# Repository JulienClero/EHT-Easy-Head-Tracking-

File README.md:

# EHT (Easy Head Tracking)

A DIY head tracking system using ESP32 and MPU6050 for gaming and simulations, compatible with OpenTrack.

## 🎯 Features

- **3DOF Tracking**: Yaw, Pitch, Roll with gyroscope, accelerometer and magnetometer
- **WiFi Transmission**: Real-time UDP data streaming
- **Complementary Filter**: Eliminates drift on pitch/roll
- **Start Up Yaw Calibartion**: Minimizes yaw drift
- **Low Latency**: Less than 20ms end-to-end
- **OpenTrack Compatible**: Plug & play with games and simulators

## 🔧 Components

### Current Version (v1.0)
- **ESP32** (DevKit v1 or similar) - ~$8
- **MPU6050** (accelerometer + gyroscope) - ~$3
- **4 jumper wires** female-female - ~$2
- **Case/mount** (3D printing recommended) - ~$2

### Future Version (v2.0) - In Development
- **ESP32-S3 N4** - ~$3.8 (JLCPCB)
- **ICM-20948** (9-axis, accelerometer + gyroscope + magnetometer) - ~$4.5
- **EHT Custom PCB** (currently being designed)
- **Li-Ion Battery** (500-1000mAh)
- **Charging Circuit** (integrated PCB)
- **ON/OFF Switch**
- **Custom Case** (3D printed) - <$1

## 📐 Wiring Diagram

### Version v1.0 (Prototype)
```
ESP32          MPU6050
-----          -------
3.3V    ---    VCC
GND     ---    GND
GPIO21  ---    SDA
GPIO22  ---    SCL
```

### Version v2.0 (Custom PCB)
*Detailed schematic available with custom PCB*

## 🚀 Installation

### 1. Prepare Environment
```bash
# Install Arduino IDE
# Add ESP32 support:
# File > Preferences > Additional Board Manager URLs
# https://dl.espressif.com/dl/package_esp32_index.json
```

### 2. Configure Code
```cpp
// Modify these variables in the code:
const char* ssid     = "YOUR_WIFI";
const char* password = "YOUR_PASSWORD";
IPAddress pcIP(192, 168, 1, XXX);  // Your PC IP
```

### 3. Flash ESP32
- Select board: `ESP32 Dev Module`
- Select serial port
- Make modifications to the code : Fill in your wifi ssid, password and your PC's IP adress (2. Configure Code)
- Compile and upload

## 🎮 OpenTrack Configuration

### 1. Install OpenTrack
Download from: https://github.com/opentrack/opentrack/releases

### 2. Configuration
1. **Input**: `UDP over network`
   - Port: `4242`
   - Bind address: `0.0.0.0`

2. **Output**: Choose according to your game
   - `freetrack 2.0 Enhanced` (most games)
   - `TrackIR` (for compatible games)

3. **Mapping**: Adjust to your preferences

### 3. Use
- Switch on your EHT
- Stay still while it calibrates (10 sec default)
- Start OpenTrack
- Click "Start"
- You should see the octopus move with your head

## 📊 Performance

- **Frequency**: 100Hz (10ms per sample)
- **Total Latency**: < 20ms
- **Accuracy**: ±1° (pitch/roll), ±2° (yaw)
- **Drift**: None on pitch/roll, slight on yaw

## 🔧 Advanced Settings (v1.0)

### Sensitivity Adjustment
```cpp
// In code, final lines:
headData[0] = yaw * 2.0;   // Multiply for more sensitivity
headData[1] = pitch * 3.0;
headData[2] = roll * 3.0;
```

### Complementary Filter
```cpp
const float alpha = 0.99f;  // 0.95-0.99 recommended
// Closer to 1.0 = more responsive but more noise
// Closer to 0.9 = more stable but less responsive
```

## 🛠️ Troubleshooting

### WiFi Connection Issues
- Check SSID/password
- Verify ESP32 is on same network
- Restart router if necessary

### Angle Drift
- **Pitch/Roll**: No drift (complementary filter)
- **Yaw**: Normal drift without magnetometer
- Solution: Recalibrate with `Ctrl+Home` in OpenTrack

### Erratic Data
- Check I2C connections
- Add decoupling capacitors if needed
- Verify stable 3.3V power supply

### High Latency
- Reduce `LOOP_INTERVAL_MS` (watch CPU load)
- Use 5GHz WiFi if possible
- Disable WiFi sleep mode

## 🤝 Contributing

Contributions are welcome! Feel free to:
- Report bugs
- Suggest improvements
- Share hardware modifications
- Add support for more games

## 📄 License

See the `LICENSE` file for details.

## 🎮 Tested Games

- ✅ **DCS World** (freetrack)
- ✅ **Star Citizen** (freetrack)

## 🔮 Roadmap

### Version 1.0 (Current) ✅
- [x] 3DOF tracking (Yaw, Pitch, Roll)
- [x] WiFi UDP transmission
- [x] Complementary filter
- [x] Yaw Calibration
- [x] OpenTrack compatibility

### Version 2.0 (Planned)
- [ ] **EHT Custom PCB** - Compact and professional design
- [ ] **Magnetometer support** - Eliminates yaw drift
- [ ] **Integrated battery** - 8-12h autonomy
- [ ] **USB-C charging circuit** - Fast charging
- [ ] **Status LEDs or Small OLED Screen** - Battery, WiFi, tracking

---

**⚠️ Important**: This project is for personal use. Please respect the terms of use of games and simulators.

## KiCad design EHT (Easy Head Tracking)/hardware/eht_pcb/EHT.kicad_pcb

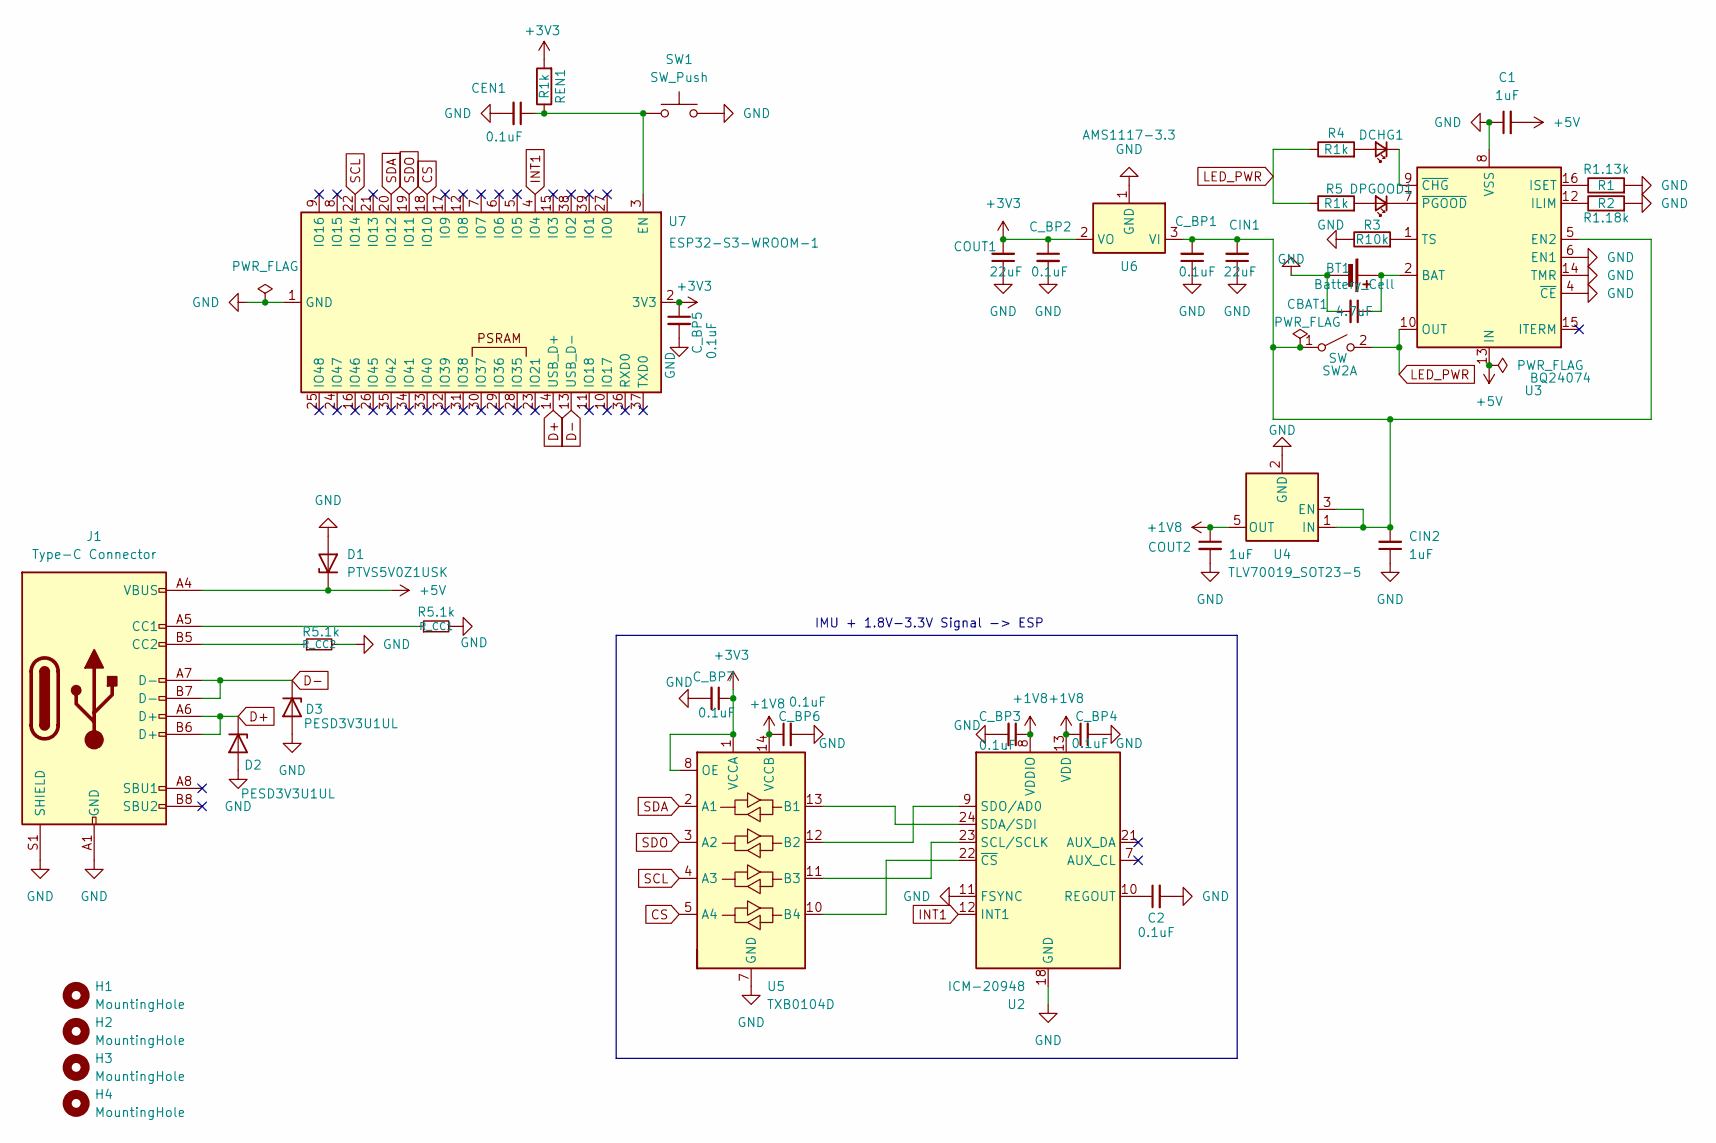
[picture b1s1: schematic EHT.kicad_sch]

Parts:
BT1: Battery_Cell
C1: 1uF; C_0603_1608Metric
C2: 0.1uF; C_0603_1608Metric
CBAT1: 4.7uF; C_0603_1608Metric
CEN1: 0.1uF; C_0603_1608Metric
CIN1: 22uF; C_0603_1608Metric
CIN2: 1uF; C_0603_1608Metric
COUT1: 22uF; C_0603_1608Metric
COUT2: 1uF; C_0603_1608Metric
C_BP1, C_BP2, C_BP3, C_BP4, C_BP5, C_BP6, C_BP7: 0.1uF; C_0603_1608Metric
D1: PTVS5V0Z1USK; Nexperia_DSN1608-2_1.6x0.8mm
D2, D3: PESD3V3U1UL; D_SOD-882
DCHG1: LED; LED_0805_2012Metric
DPGOOD1: LED; LED_0805_2012Metric
H1, H2, H3, H4: MountingHole; MountingHole_2.2mm_M2
J1: Type-C Connector; USB_C_Receptacle_GCT_USB4105-xx-A_16P_TopMnt_Horizontal
R1: R1.13k; R_0603_1608Metric
R2: R1.18k; R_0603_1608Metric
R3: R10k; R_0603_1608Metric
R4, R5: R1k; R_0603_1608Metric
REN1: R1k; R_0603_1608Metric
R_CC1, R_CC2: R5.1k; R_0603_1608Metric
SW1: SW_Push; SW_PUSH_1P1T_6x3.5mm_H4.3_APEM_MJTP1243
SW2: SW; SW_DIP_SPSTx01_Slide_Copal_CHS-01A_W5.08mm_P1.27mm_JPin
U2: ICM-20948; InvenSense_QFN-24_3x3mm_P0.4mm
U3: BQ24074; VQFN-16-1EP_3x3mm_P0.5mm_EP1.6x1.6mm
U4: TLV70019_SOT23-5; SOT-23-5
U5: TXB0104D; SOIC-14_3.9x8.7mm_P1.27mm
U6: AMS1117-3.3; SOT-223-3_TabPin2
U7: ESP32-S3-WROOM-1

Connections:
+1V8: COUT2.1, C_BP3.1, C_BP4.1, C_BP6.1, U2.8 (VDDIO), U2.13 (VDD), U4.5 (OUT), U5.14 (VCCB)
+3V3: COUT1.2, C_BP2.1, C_BP5.1, C_BP7.1, REN1.2, U5.1 (VCCA), U5.8 (OE), U6.2 (VO), U7.2 (3V3)
+5V: C1.2, D1.1 (K), J1.A4 (VBUS), J1.A9 (VBUS), J1.B4 (VBUS), J1.B9 (VBUS), U3.13 (IN)
CS: U5.5 (A4), U7.18 (IO10)
D+: D2.1 (K), J1.A6 (D+), J1.B6 (D+), U7.14 (USB_D+)
D-: D3.1 (K), J1.A7 (D-), J1.B7 (D-), U7.13 (USB_D-)
GND: BT1.2 (-), C1.1, C2.2, CBAT1.2, CEN1.2, CIN1.1, CIN2.1, COUT1.1, COUT2.2, C_BP1.1, C_BP2.2, C_BP3.2, C_BP4.2, C_BP5.2, C_BP6.2, C_BP7.2, D1.2 (A), D2.2 (A), D3.2 (A), J1.A1 (GND), J1.A12 (GND), J1.B1 (GND), J1.B12 (GND), J1.S1 (SHIELD), R1.2, R2.2, R3.1, R_CC1.2, R_CC2.2, SW1.2, U2.11 (FSYNC), U2.18 (GND), U2.20 (GND), U3.4 (~CE), U3.6 (EN1), U3.8 (VSS), U3.14 (TMR), U3.17 (VSS), U4.2 (GND), U5.7 (GND), U6.1 (GND), U7.1 (GND), U7.40 (GND), U7.41 (GND); also elsewhere on the board
INT1: U2.12 (INT1), U7.4 (IO4)
LED_PWR: R4.1, R5.1, SW2.2 (B), U3.10 (OUT), U3.11 (OUT)
unnamed 9: BT1.1 (+), CBAT1.1, U3.2 (BAT), U3.3 (BAT); also elsewhere on the board
unnamed: DCHG1.2 (A), R4.2
unnamed: DCHG1.1 (K), U3.9 (~CHG)
unnamed: DPGOOD1.2 (A), R5.2
unnamed: DPGOOD1.1 (K), U3.7 (~PGOOD)
unnamed: J1.A5 (CC1), R_CC1.1
unnamed: J1.B5 (CC2), R_CC2.1
unnamed: CIN1.2, CIN2.2, C_BP1.2, SW2.1 (A), U3.5 (EN2), U4.1 (IN), U4.3 (EN), U6.3 (VI)
unnamed: C2.1, U2.10 (REGOUT)
unnamed: U2.23 (SCL/SCLK), U5.11 (B3)
unnamed: U2.24 (SDA/SDI), U5.13 (B1)
unnamed: U2.9 (SDO/AD0), U5.12 (B2)
unnamed: U2.22 (~CS), U5.10 (B4)
unnamed: R2.1, U3.12 (ILIM)
unnamed: R1.1, U3.16 (ISET)
unnamed: R3.2, U3.1 (TS)
unnamed: CEN1.1, REN1.1, SW1.1, U7.3 (EN)
SCL: U5.4 (A3), U7.22 (IO14)
SDA: U5.2 (A1), U7.20 (IO12)
SDO: U5.3 (A2), U7.19 (IO11)

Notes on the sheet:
IMU + 1.8V-3.3V Signal -> ESP

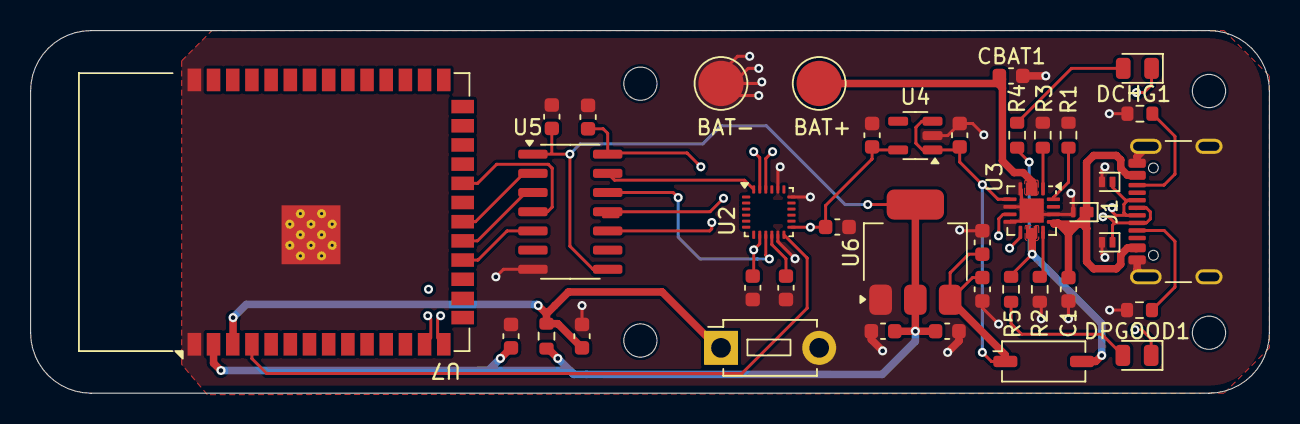
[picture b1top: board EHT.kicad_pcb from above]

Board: 4 copper layers, 82.0 x 24.0 mm, 43 parts (0 on the bottom side), 29 nets.

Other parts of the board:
BAT+: TestPoint_Pad_D3.0mm
BAT-: TestPoint_Pad_D3.0mm

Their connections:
GND: BAT-.1; also elsewhere on the board
unnamed 9: BAT+.1; also elsewhere on the board

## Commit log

2025-08-04 Update eht_v1.ino
    Updated low level approach using both cores of the ESP32 chip and a custom MPU6050 interface (Because it is not realy an MPU6050 and libraries don't work, you can change this part and use libraries).
2025-08-04 Added EHT MOUNT for Logitech G935
    A basic stl file of a 3d printable mount for EHT adapted ont my G935 headset.
2025-08-07 Create LICENSE
2025-09-02 Added documentation, Circuit diagram, PCB Gerber...
2025-09-02 Added, PCB files and documentation
